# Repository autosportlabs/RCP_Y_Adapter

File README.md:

RCPYAdapter
===========

Y cable adapter to allow RaceCapture/Pro to work with a bluetooth adapter and the Realtime cellular module

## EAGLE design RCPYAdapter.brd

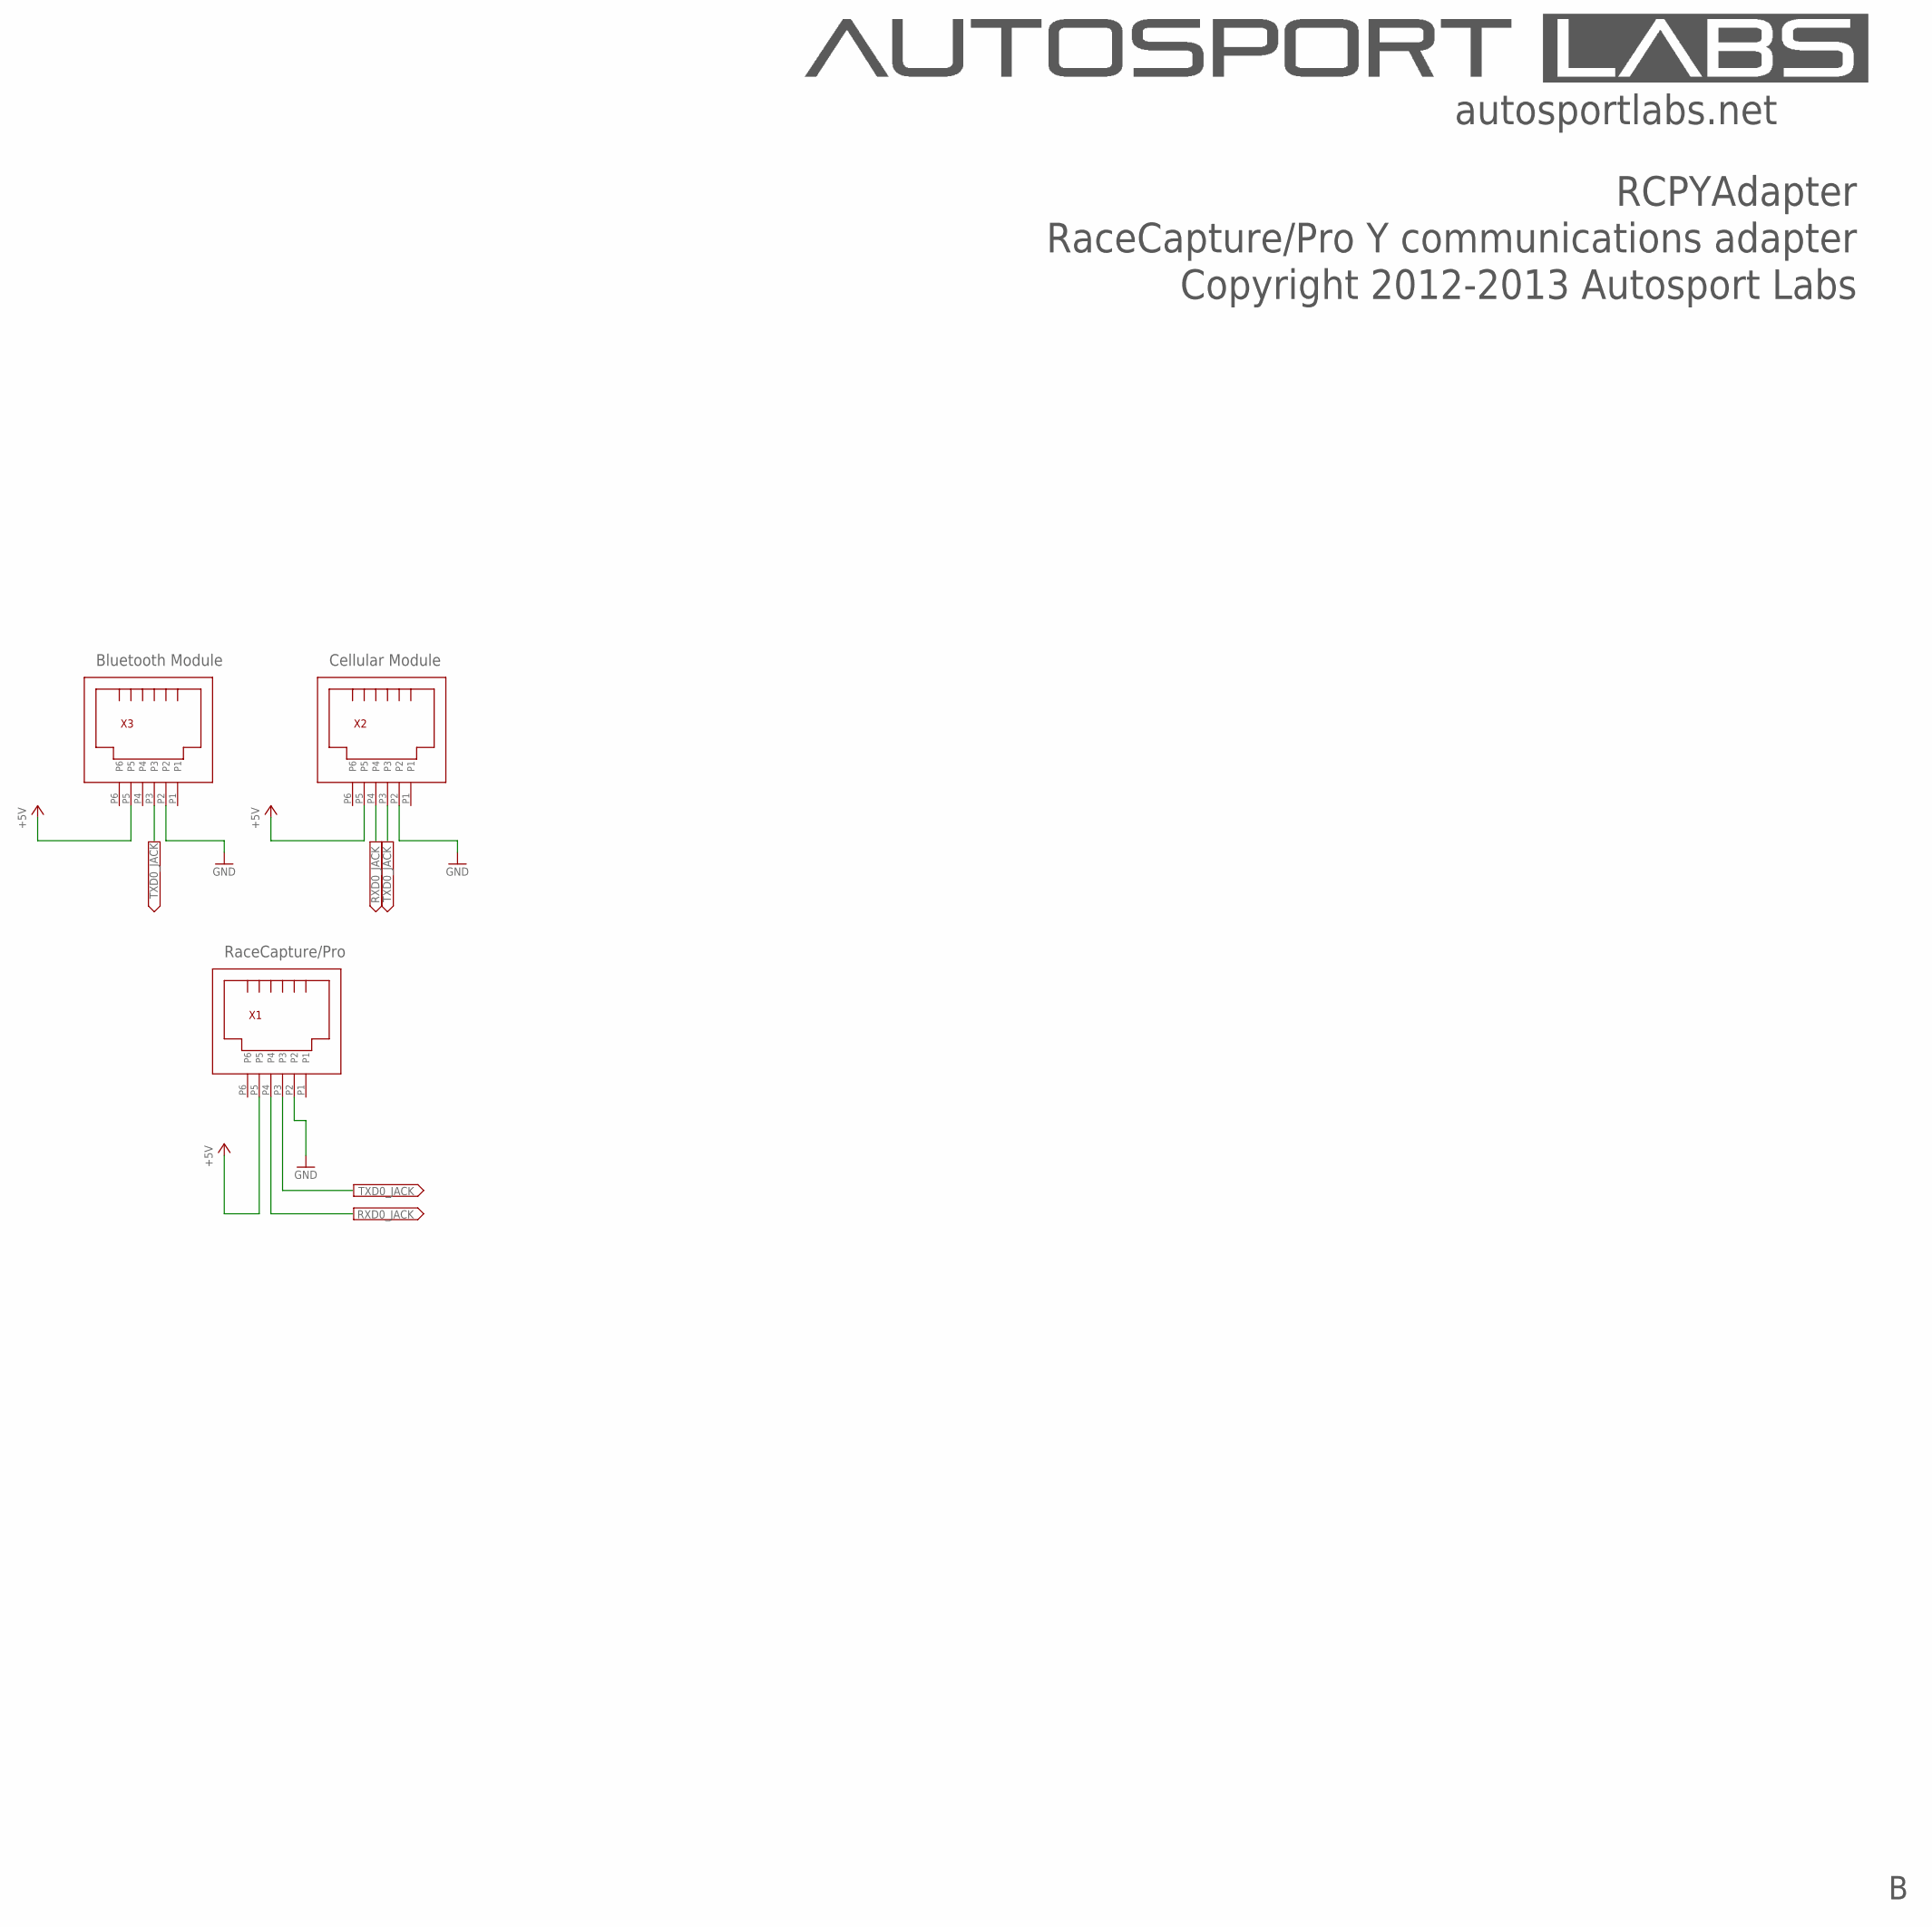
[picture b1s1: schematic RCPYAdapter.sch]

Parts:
X1, X2, X3: FCI_88400_066LF_RJ12_4POS; RJ12_RIGHT_ANGLE_PCB

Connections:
+5V: X1.P5, X2.P5, X3.P5
GND: X1.P2, X2.P2, X3.P2
RXD0_JACK: X1.P4, X2.P4
TXD0_JACK: X1.P3, X2.P3, X3.P3

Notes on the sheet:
Copyright 2012-2013 Autosport Labs
RCPYAdapter
autosportlabs.net
RaceCapture/Pro Y communications adapter
RaceCapture/Pro
Bluetooth Module
Cellular Module

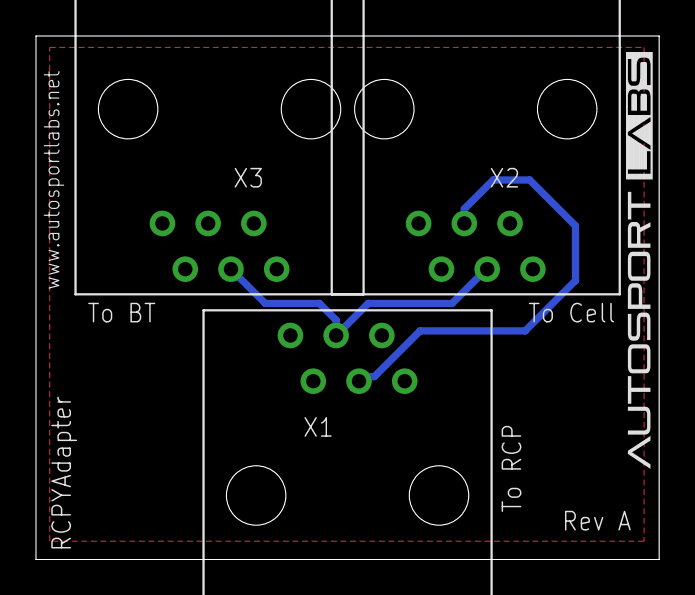
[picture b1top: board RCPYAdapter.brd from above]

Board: 2 copper layers, 34.6 x 29.1 mm, 3 parts (0 on the bottom side), 4 nets.

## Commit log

2013-10-18 added base files
2014-01-25 corrected inverted Y adapter traces, resized board for standard size
